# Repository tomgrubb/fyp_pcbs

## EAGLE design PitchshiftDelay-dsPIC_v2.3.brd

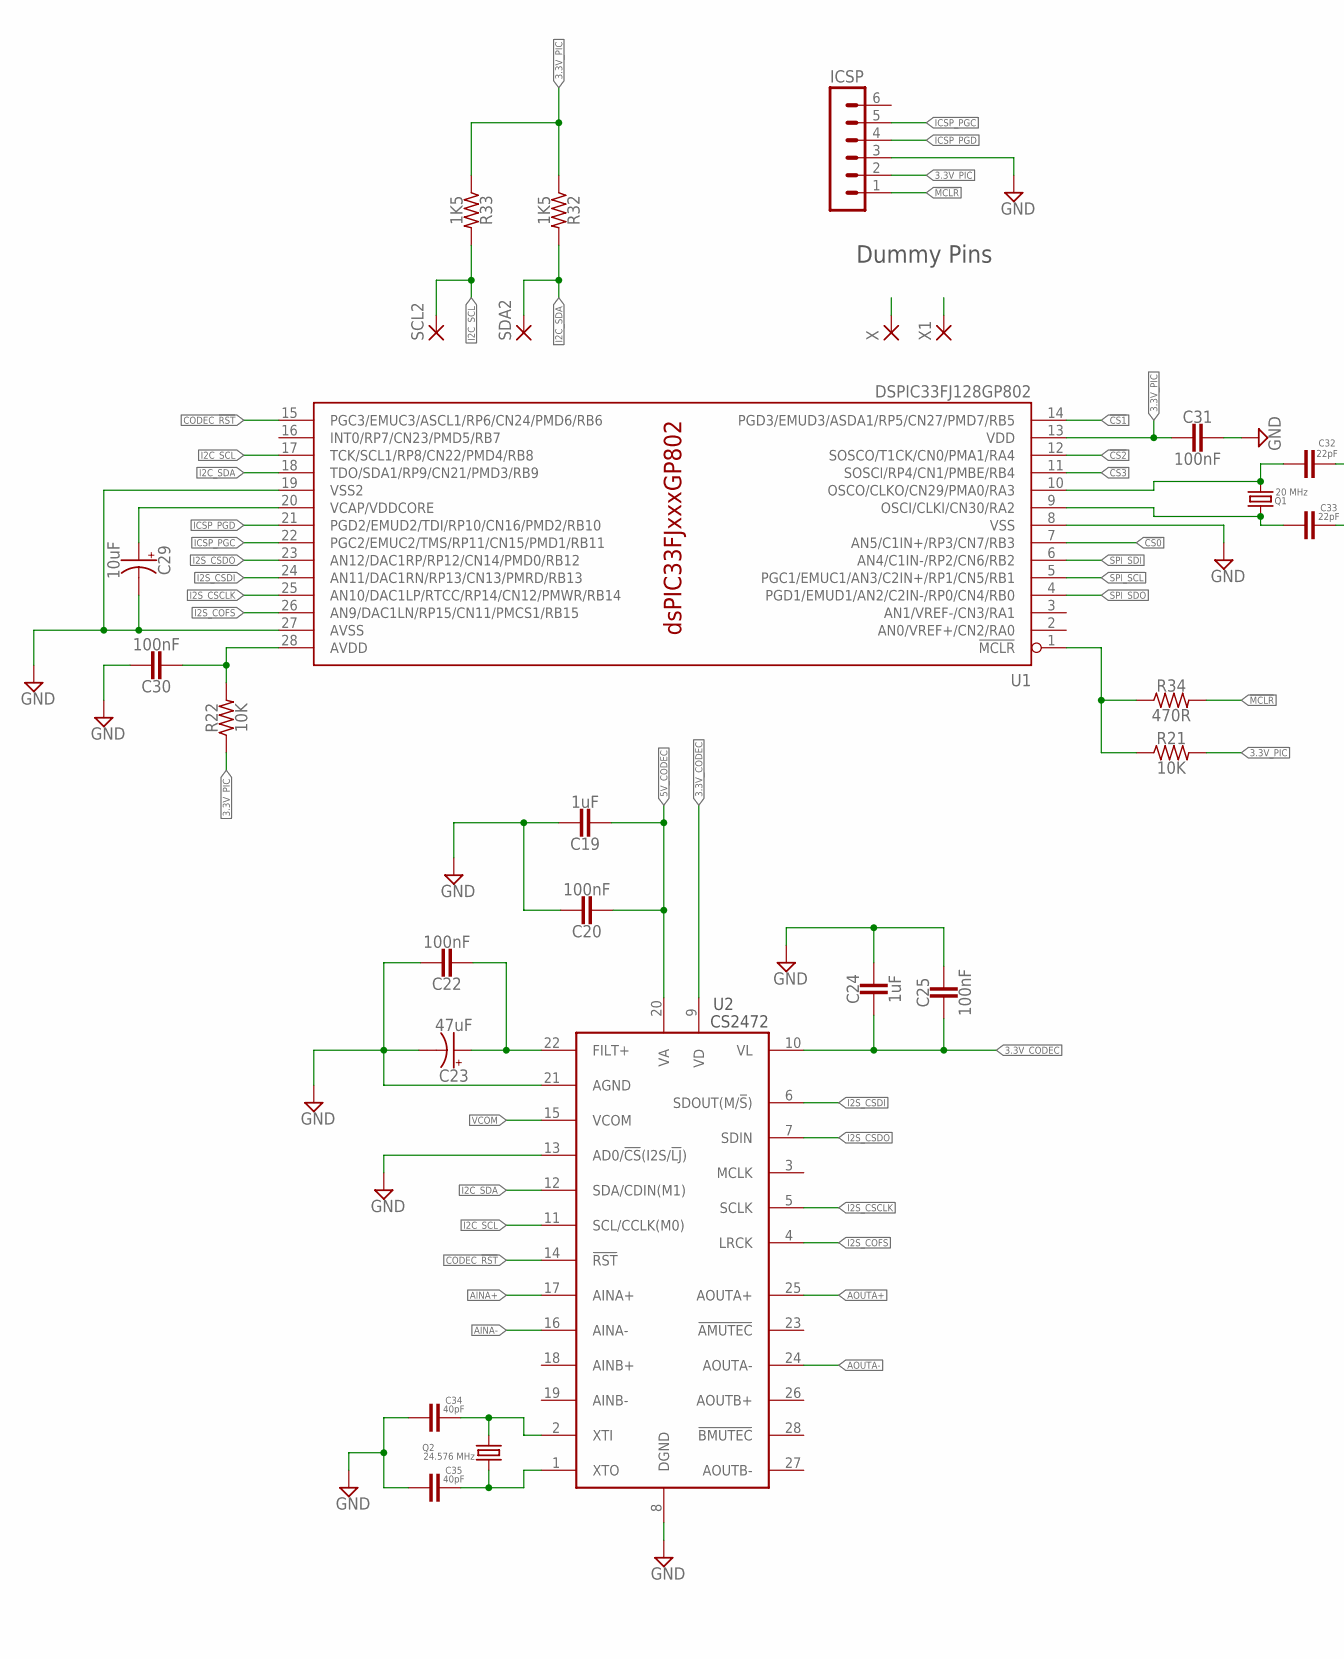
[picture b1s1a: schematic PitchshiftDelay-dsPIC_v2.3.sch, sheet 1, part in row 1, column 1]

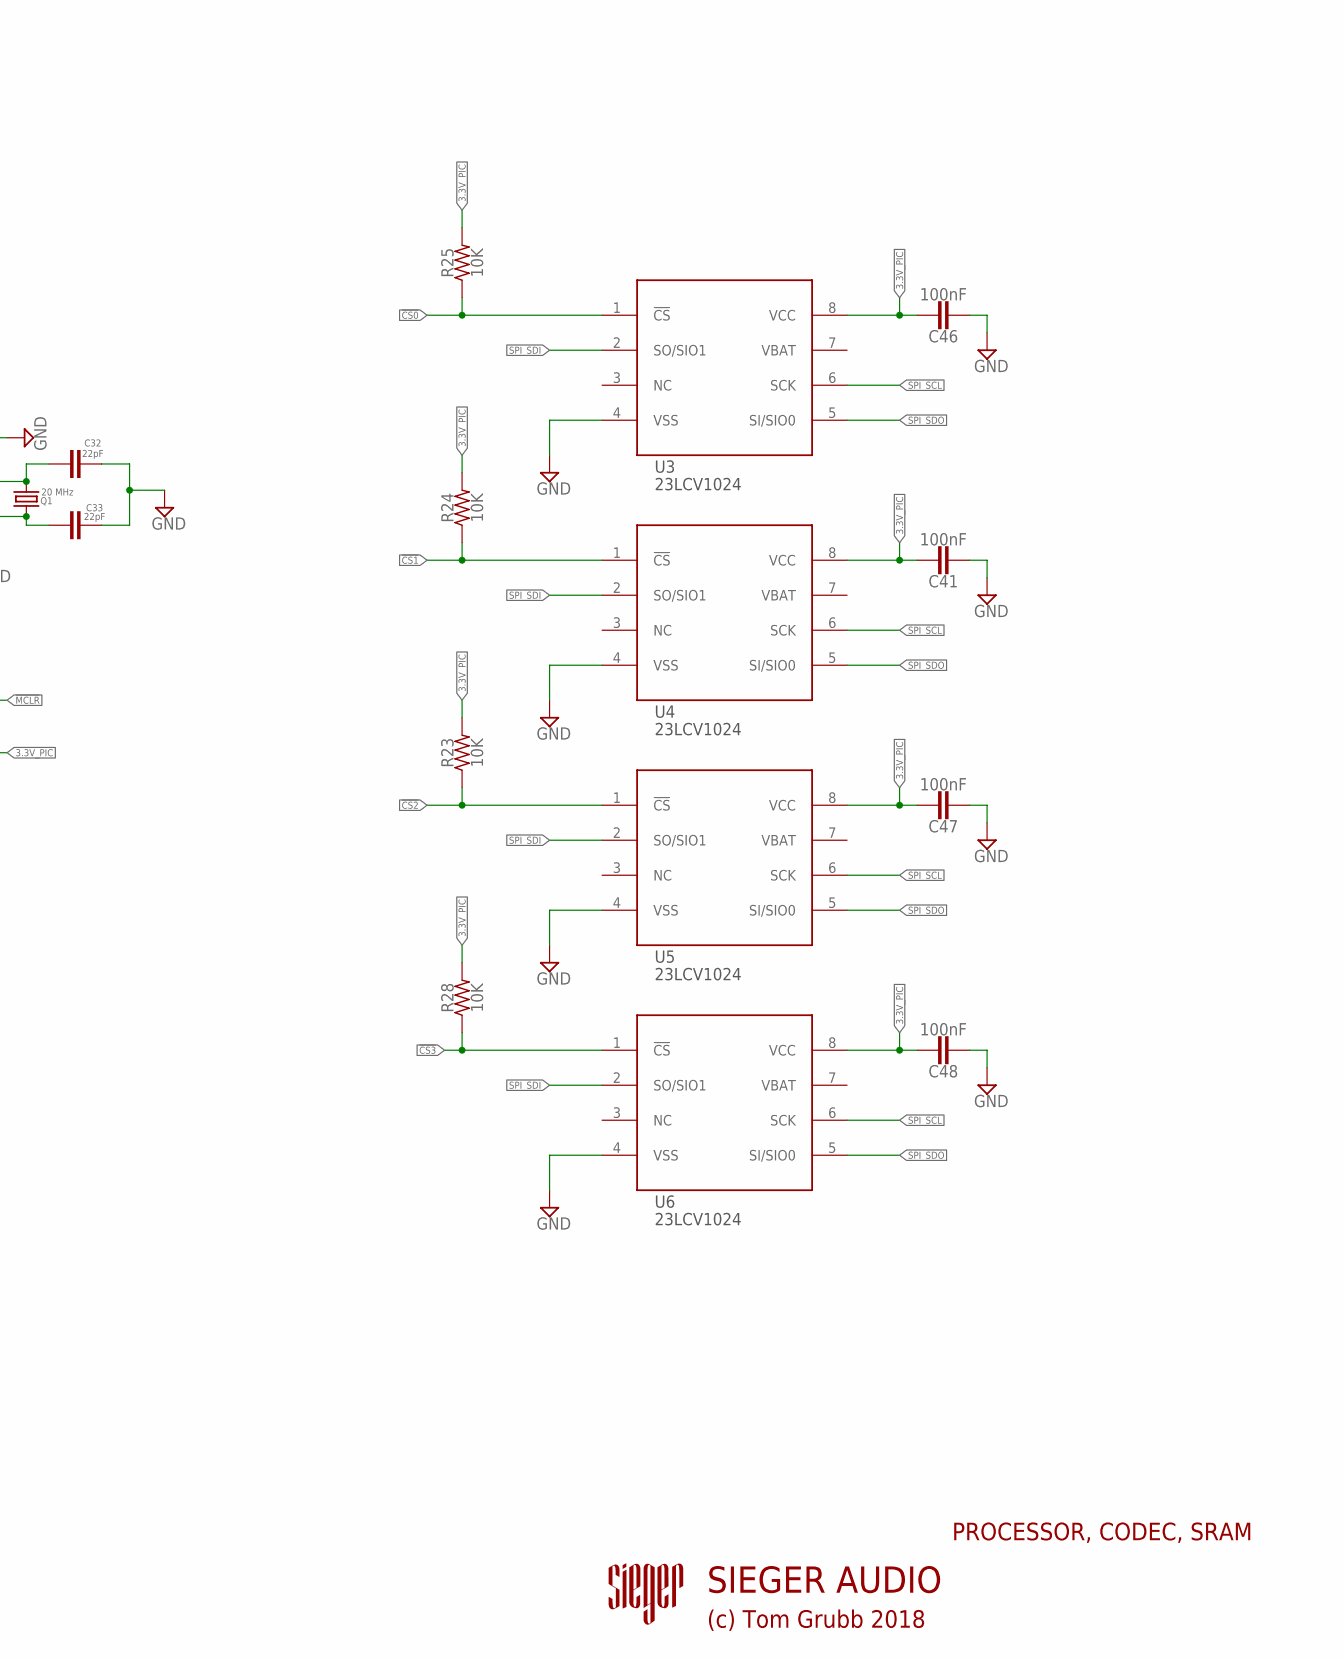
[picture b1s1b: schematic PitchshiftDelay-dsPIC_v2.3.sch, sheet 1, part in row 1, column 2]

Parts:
C19, C24: 1uF; 050X030_025
C20, C22, C25, C30, C31, C41, C46, C47, C48: 100nF; 050X030_025
C23: 47uF; 050_020_1
C29: 10uF; 050_020_1B
C32, C33: 22pF; 0805
C34, C35: 40pF; 0805
ICSP: MA06-1
Q1: 20 MHz; HC49U-V
Q2: 24.576 MHz; HC49U-V
R21, R22, R23, R24, R25, R28: 10K; RESISTOR_C0805
R32, R33: 1K5; RESISTOR_C0805
R34: 470R; RESISTOR_C0805
SCL2: 2,15/1,0
SDA2: 2,15/1,0
U1: DSPIC33FJ128GP802; SO28W
U2: CS2472; TSSOP28L
U3, U4, U5, U6: 23LCV1024; SOIC8
X, X1: 2,15/1,0

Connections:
3.3V_CODEC: C24.2, C25.2, U2.9 (VD), U2.10 (VL); also elsewhere on the board
3.3V_PIC: C31.2, C41.1, C46.1, C47.1, C48.1, ICSP.2, R21.2, R22.1, R23.2, R24.2, R25.2, R28.2, R32.1, R33.1, U1.13 (VDD), U3.8 (VCC), U4.8 (VCC), U5.8 (VCC), U6.8 (VCC); also elsewhere on the board
5V_CODEC: C19.2, C20.2, U2.20 (VA); also elsewhere on the board
!CS0: R25.1, U1.7 (AN5/C1IN+/RP3/CN7/RB3), U3.1 (!CS)
!CS1: R24.1, U1.14 (PGD3/EMUD3/ASDA1/RP5/CN27/PMD7/RB5), U4.1 (!CS)
!CS2: R23.1, U1.12 (SOSCO/T1CK/CN0/PMA1/RA4), U5.1 (!CS)
!CS3: R28.1, U1.11 (SOSCI/RP4/CN1/PMBE/RB4), U6.1 (!CS)
!MCLR: ICSP.1, R34.2
AINA+: U2.17 (AINA+); also elsewhere on the board
AINA-: U2.16 (AINA-); also elsewhere on the board
AOUTA+: U2.25 (AOUTA+); also elsewhere on the board
AOUTA-: U2.24 (AOUTA-); also elsewhere on the board
CODEC_!RST: U1.15 (PGC3/EMUC3/ASCL1/RP6/CN24/PMD6/RB6), U2.14 (!RST)
FILT+: C22.2, C23.+, U2.22 (FILT+)
GND: C19.1, C20.1, C22.1, C23.-, C24.1, C25.1, C29.-, C30.1, C31.1, C32.1, C33.1, C34.2, C35.2, C41.2, C46.2, C47.2, C48.2, ICSP.3, U1.8 (VSS), U1.19 (VSS2), U1.27 (AVSS), U2.8 (DGND), U2.13 (AD0/!CS!(I2S/!LJ!)), U2.21 (AGND), U3.4 (VSS), U4.4 (VSS), U5.4 (VSS), U6.4 (VSS); also elsewhere on the board
I2C_SCL: R33.2, SCL2.1, U1.17 (TCK/SCL1/RP8/CN22/PMD4/RB8), U2.11 (SCL/CCLK(M0)), X.1
I2C_SDA: R32.2, SDA2.1, U1.18 (TDO/SDA1/RP9/CN21/PMD3/RB9), U2.12 (SDA/CDIN(M1))
I2S_COFS: U1.26 (AN9/DAC1LN/RP15/CN11/PMCS1/RB15), U2.4 (LRCK)
I2S_CSCLK: U1.25 (AN10/DAC1LP/RTCC/RP14/CN12/PMWR/RB14), U2.5 (SCLK)
I2S_CSDI: U1.24 (AN11/DAC1RN/RP13/CN13/PMRD/RB13), U2.6 (SDOUT(M/!S!))
I2S_CSDO: U1.23 (AN12/DAC1RP/RP12/CN14/PMD0/RB12), U2.7 (SDIN)
ICSP_PGC: ICSP.5, U1.22 (PGC2/EMUC2/TMS/RP11/CN15/PMD1/RB11)
ICSP_PGD: ICSP.4, U1.21 (PGD2/EMUD2/TDI/RP10/CN16/PMD2/RB10)
unnamed: C30.2, R22.2, U1.28 (AVDD)
unnamed: C29.+, U1.20 (VCAP/VDDCORE)
unnamed: C33.2, Q1.1, U1.9 (OSCI/CLKI/CN30/RA2)
unnamed: C32.2, Q1.2, U1.10 (OSCO/CLKO/CN29/PMA0/RA3)
unnamed: R21.1, R34.1, U1.1 (!MCLR)
unnamed: C34.1, Q2.2, U2.2 (XTI)
unnamed: C35.1, Q2.1, U2.1 (XTO)
SPI_SCL: U1.5 (PGC1/EMUC1/AN3/C2IN+/RP1/CN5/RB1), U3.6 (SCK), U4.6 (SCK), U5.6 (SCK), U6.6 (SCK)
SPI_SDI: U1.6 (AN4/C1IN-/RP2/CN6/RB2), U3.2 (SO/SIO1), U4.2 (SO/SIO1), U5.2 (SO/SIO1), U6.2 (SO/SIO1)
SPI_SDO: U1.4 (PGD1/EMUD1/AN2/C2IN-/RP0/CN4/RB0), U3.5 (SI/SIO0), U4.5 (SI/SIO0), U5.5 (SI/SIO0), U6.5 (SI/SIO0)
VCOM: U2.15 (VCOM); also elsewhere on the board

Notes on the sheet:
PROCESSOR, CODEC, SRAM
Dummy Pins
(c) Tom Grubb 2018
SIEGER AUDIO

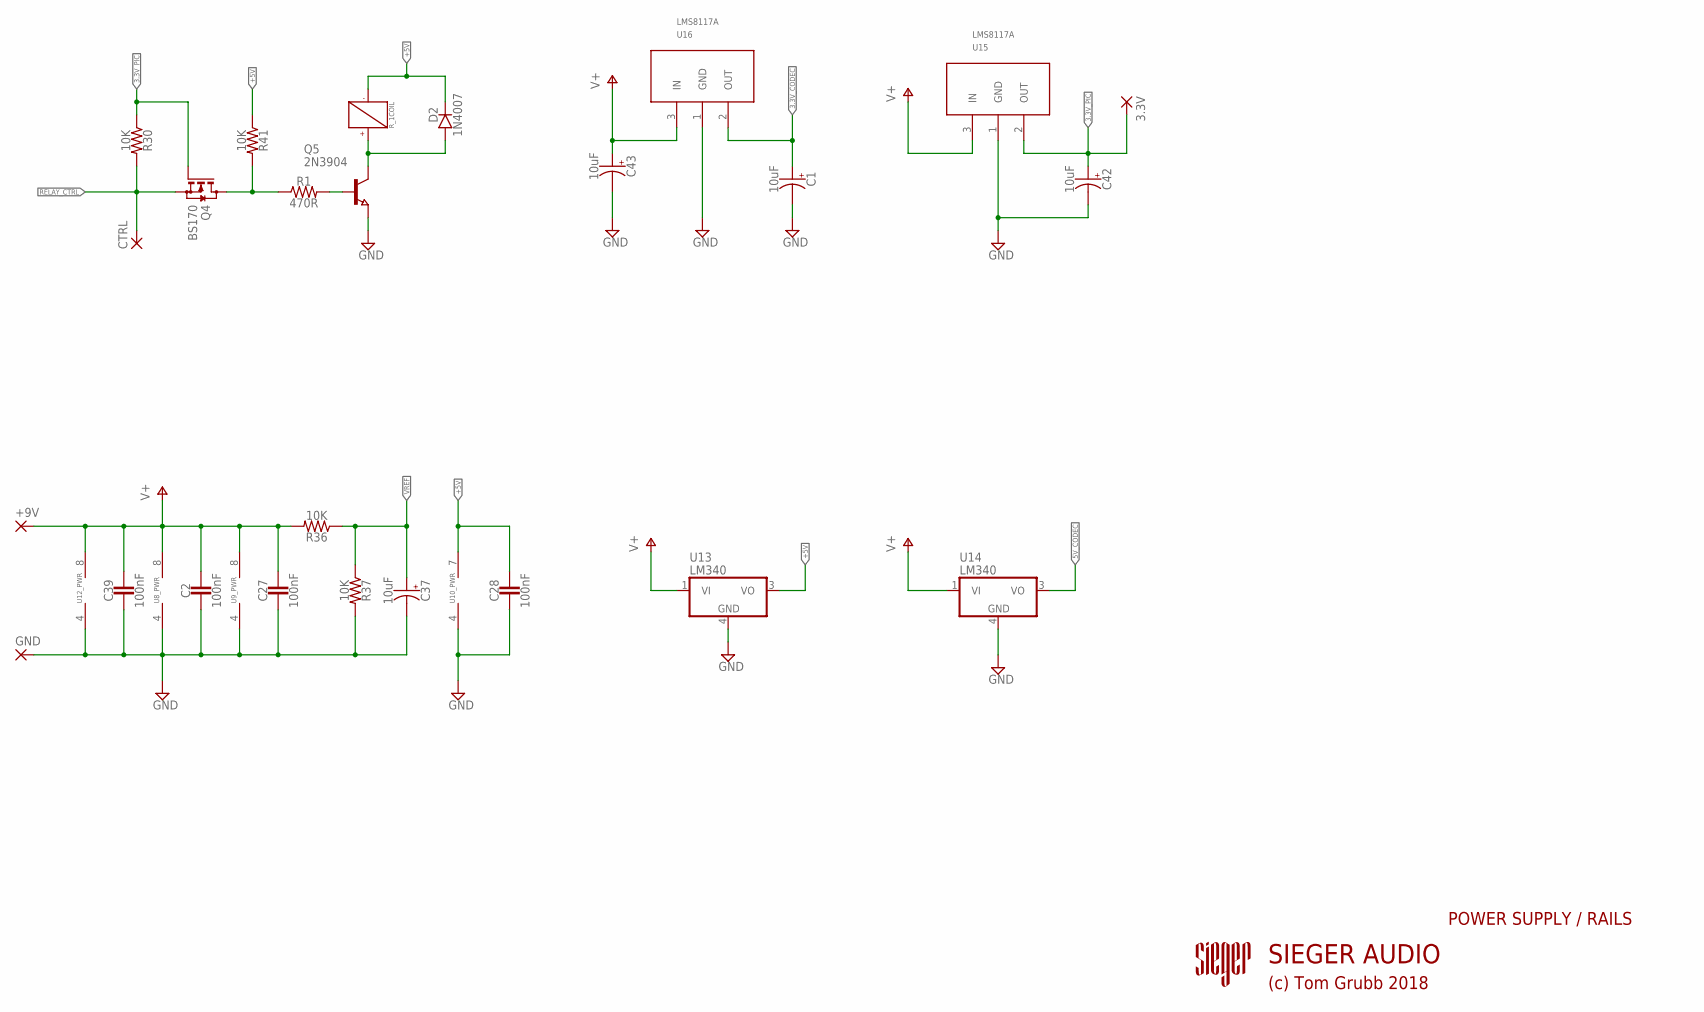
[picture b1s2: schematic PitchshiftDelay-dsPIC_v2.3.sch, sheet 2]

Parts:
3.3V: 2,15/1,0
+9V: 2,15/1,0
C1, C37, C42, C43: 10uF; 050_020_1
C2, C27, C28, C39: 100nF; 050X030_025
CTRL: 2,15/1,0
D2: 1N4007; DO35-3
GND: 2,15/1,0
Q4: BS170; SOT23
Q5: 2N3904; SOT23
R1: 470R; RESISTOR_C0805
R30, R36, R37, R41: 10K; RESISTOR_C0805
R_1: AL5WNK_2; 10PIN
U8, U9, U12: LF353; SO08
U10: OP1177; MSOP8
U13, U14: LM340; SOT223
U15, U16: LMS8117A; SOT223

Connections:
3.3V_CODEC: C1.+, U16.2 (OUT); also elsewhere on the board
3.3V_PIC: 3.3V.1, C42.+, Q4.1 (G), R30.1, U15.2 (OUT); also elsewhere on the board
5V_CODEC: U14.3 (VO); also elsewhere on the board
+5V: C28.1, D2.C, R41.1, R_1.P$10 (-), U10.7 (V+), U13.3 (VO); also elsewhere on the board
GND: C1.-, C2.2, C27.2, C28.2, C37.-, C39.2, C42.-, C43.-, GND.1, Q5.2 (E), R37.2, U8.4 (V-), U9.4 (V-), U10.4 (V-), U12.4 (V-), U13.4 (GND), U14.4 (GND), U15.1 (GND), U16.1 (GND); also elsewhere on the board
unnamed: Q5.1 (B), R1.2
unnamed: D2.A, Q5.3 (C), R_1.P$1 (+)
unnamed: Q4.3 (D), R1.1, R41.2
RELAY_CTRL: CTRL.1, Q4.2 (S), R30.2
V+: +9V.1, C2.1, C27.1, C39.1, C43.+, R36.2, U8.8 (V+), U9.8 (V+), U12.8 (V+), U13.1 (VI), U14.1 (VI), U15.3 (IN), U16.3 (IN)
VREF: C37.+, R36.1, R37.1; also elsewhere on the board

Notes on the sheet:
POWER SUPPLY / RAILS
(c) Tom Grubb 2018
SIEGER AUDIO

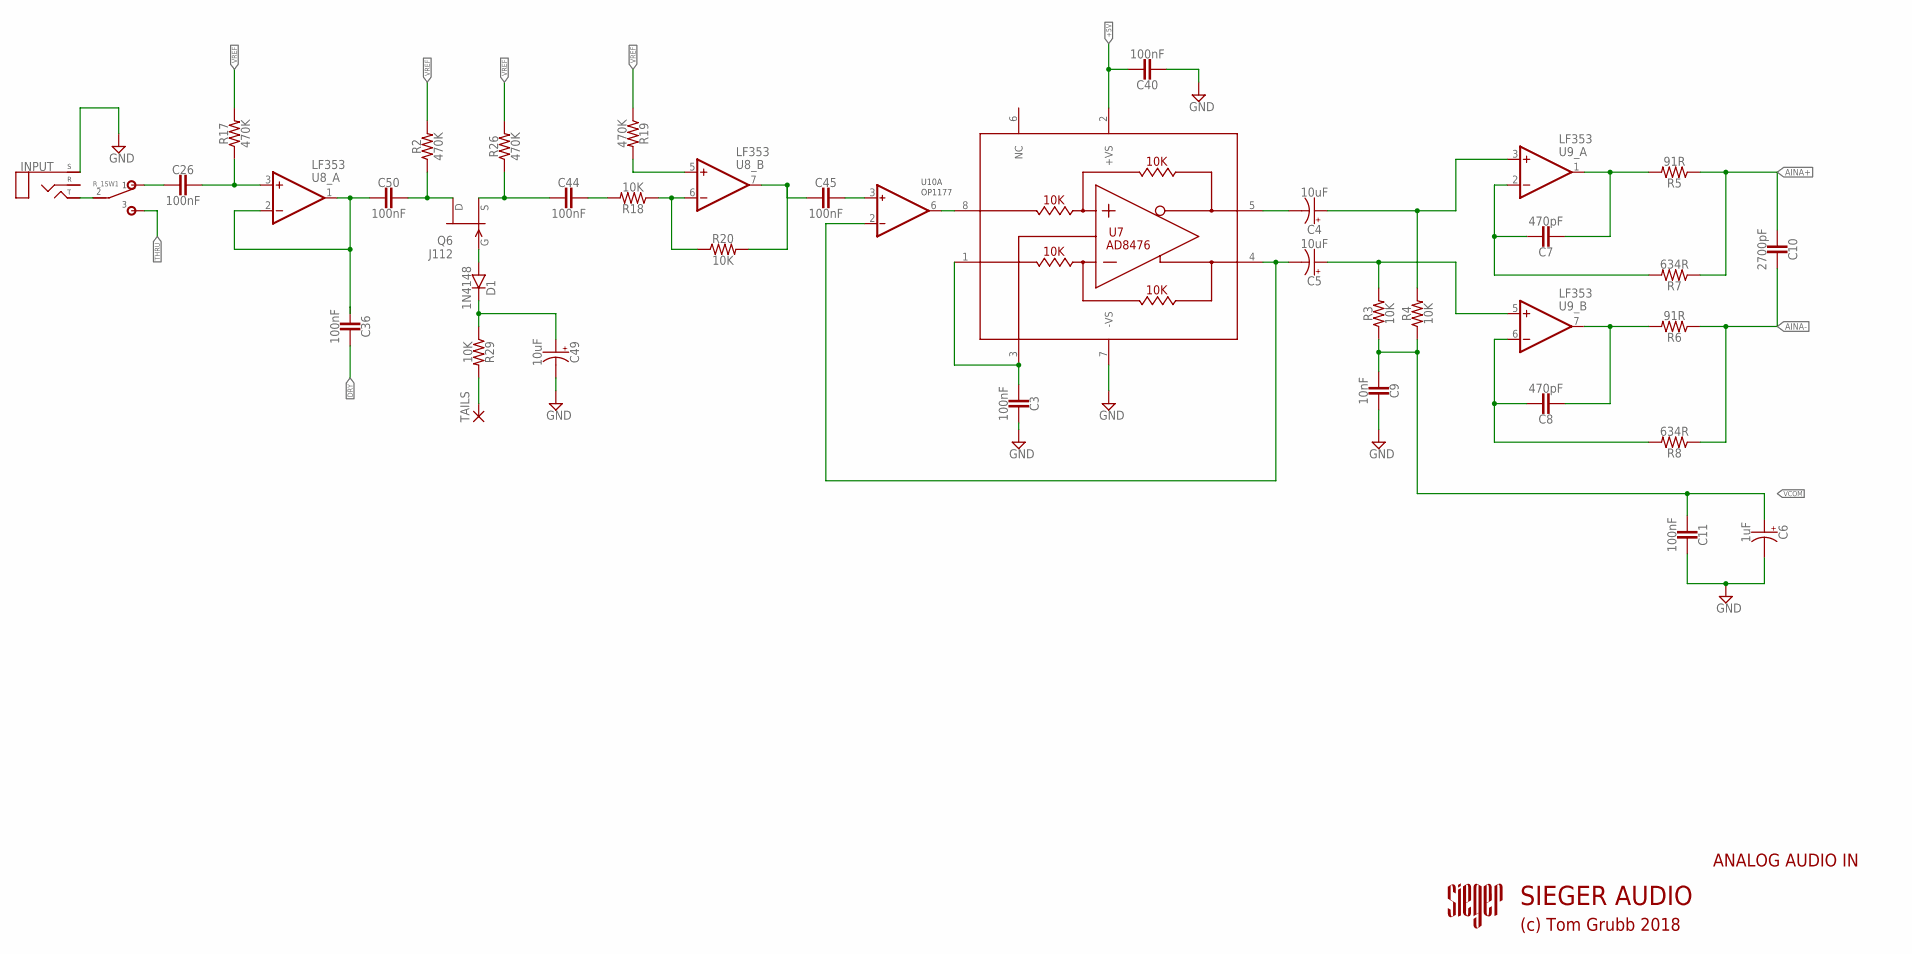
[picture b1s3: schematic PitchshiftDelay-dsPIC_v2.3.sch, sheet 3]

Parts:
C3, C11, C40: 100nF; 050X030_025
C4, C5, C49: 10uF; 050_020_1
C6: 1uF; 050_020_1
C7, C8: 470pF; BOX_SMALL
C9: 10nF; 050X030_025
C10: 2700pF; BOX_SMALL
C26, C36, C44, C45, C50: 100nF; BOX_SMALL
D1: 1N4148; DO35-3
INPUT: STEREO; STEREO_PCB
Q6: J112; SOT23
R2, R17, R19, R26: 470K; RESISTOR_C0805
R3, R4, R18, R20, R29: 10K; RESISTOR_C0805
R5, R6: 91R; RESISTOR_C0805
R7, R8: 634R; RESISTOR_C0805
R_1: AL5WNK_2; 10PIN
TAILS: 2,15/1,0
U7: AD8476; MSOP8
U8, U9: LF353; SO08
U10: OP1177; MSOP8

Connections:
+5V: C40.1, U7.2 (+VS); also elsewhere on the board
AINA+: C10.2, R5.1, R7.1; also elsewhere on the board
AINA-: C10.1, R6.1, R8.1; also elsewhere on the board
DRY: C36.1; also elsewhere on the board
GND: C3.1, C6.-, C9.1, C11.1, C40.2, C49.-, INPUT.P$1 (S), U7.7 (-VS); also elsewhere on the board
unnamed: C45.1, U10.3 (+IN)
unnamed: C3.2, U7.1 (IN-), U7.3 (VCOM)
unnamed: U7.8 (IN+), U10.6 (OUT)
unnamed: C5.-, U7.4 (+OUT), U10.2 (-IN)
unnamed: C36.2, C50.2, U8.1 (OUT), U8.2 (-IN)
unnamed: C26.1, R17.1, U8.3 (+IN)
unnamed: C4.-, U7.5 (-OUT)
unnamed: C5.+, R3.2, U9.5 (+IN)
unnamed: C4.+, R4.2, U9.3 (+IN)
unnamed: C8.1, R8.2, U9.6 (-IN)
unnamed: C8.2, R6.2, U9.7 (OUT)
unnamed: C7.1, R7.2, U9.2 (-IN)
unnamed: C7.2, R5.2, U9.1 (OUT)
unnamed: C26.2, R_1.P$2 (1)
unnamed: R18.1, R20.1, U8.6 (-IN)
unnamed: R19.2, U8.5 (+IN)
unnamed: C50.1, Q6.1 (D), R2.1
unnamed: C45.2, R20.2, U8.7 (OUT)
unnamed: C44.1, R18.2
unnamed: INPUT.P$3 (T), R_1.P$3 (2)
unnamed: C44.2, Q6.2 (S), R26.1
unnamed: C49.+, D1.C, R29.1
unnamed: D1.A, Q6.3 (G)
unnamed: R29.2, TAILS.1
THRU: R_1.P$4 (3); also elsewhere on the board
VCOM: C6.+, C9.2, C11.2, R3.1, R4.1; also elsewhere on the board
VREF: R2.2, R17.2, R19.1, R26.2; also elsewhere on the board

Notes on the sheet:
ANALOG AUDIO IN
(c) Tom Grubb 2018
SIEGER AUDIO

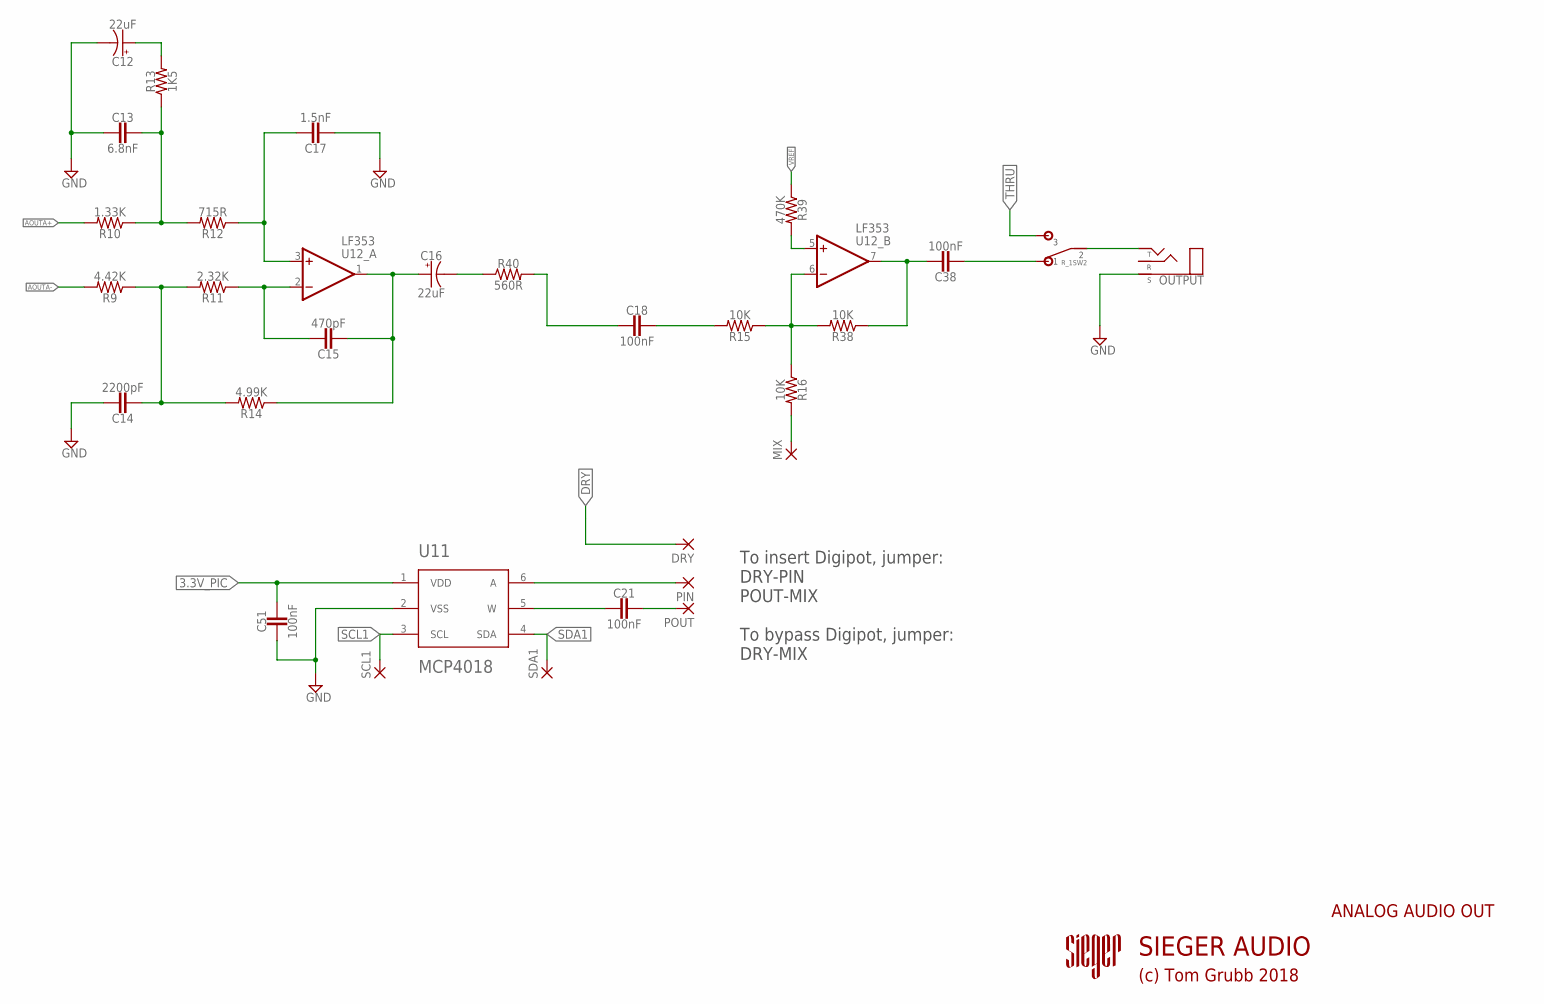
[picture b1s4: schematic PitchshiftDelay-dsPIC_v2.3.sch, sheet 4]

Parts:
C12, C16: 22uF; 050_020_1
C13: 6.8nF; BOX_SMALL
C14: 2200pF; BOX_SMALL
C15: 470pF; BOX_SMALL
C17: 1.5nF; BOX_SMALL
C18, C21, C38: 100nF; BOX_SMALL
C51: 100nF; 050X030_025
DRY: 2,15/1,0
MIX: 2,15/1,0
OUTPUT: STEREO; STEREO_PCB
PIN: 2,15/1,0
POUT: 2,15/1,0
R9: 4.42K; RESISTOR_C0805
R10: 1.33K; RESISTOR_C0805
R11: 2.32K; RESISTOR_C0805
R12: 715R; RESISTOR_C0805
R13: 1K5; RESISTOR_C0805
R14: 4.99K; RESISTOR_C0805
R15, R16, R38: 10K; RESISTOR_C0805
R39: 470K; RESISTOR_C0805
R40: 560R; RESISTOR_C0805
R_1: AL5WNK_2; 10PIN
SCL1: 2,15/1,0
SDA1: 2,15/1,0
U11: MCP4018; SC70-6
U12: LF353; SO08

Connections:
3.3V_PIC: C51.1, U11.1 (VDD); also elsewhere on the board
AMUTE: C18.2, R40.2
AOUTA+: R10.2; also elsewhere on the board
AOUTA-: R9.2; also elsewhere on the board
DRY: DRY.1; also elsewhere on the board
GND: C12.-, C13.2, C14.1, C17.2, C51.2, OUTPUT.P$1 (S), U11.2 (VSS); also elsewhere on the board
unnamed: C21.2, U11.5 (W)
unnamed: C16.-, R40.1
unnamed: C13.1, R10.1, R12.2, R13.1
unnamed: C14.2, R9.1, R11.2, R14.2
unnamed: C15.1, R11.1, U12.2 (-IN)
unnamed: C17.1, R12.1, U12.3 (+IN)
unnamed: C15.2, C16.+, R14.1, U12.1 (OUT)
unnamed: MIX.1, R16.2
unnamed: C18.1, R15.2
unnamed: C12.+, R13.2
unnamed: OUTPUT.P$3 (T), R_1.P$8 (2)
unnamed: C38.2, R_1.P$9 (1)
unnamed: PIN.1, U11.6 (A)
unnamed: R15.1, R16.1, R38.2, U12.6 (-IN)
unnamed: C38.1, R38.1, U12.7 (OUT)
unnamed: R39.2, U12.5 (+IN)
unnamed: C21.1, POUT.1
SCL1: SCL1.1, U11.3 (SCL)
SDA1: SDA1.1, U11.4 (SDA)
THRU: R_1.P$7 (3); also elsewhere on the board
VREF: R39.1; also elsewhere on the board

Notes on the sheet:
To insert Digipot, jumper: DRY-PIN POUT-MIX To bypass Digipot, jumper: DRY-MIX
ANALOG AUDIO OUT
(c) Tom Grubb 2018
SIEGER AUDIO

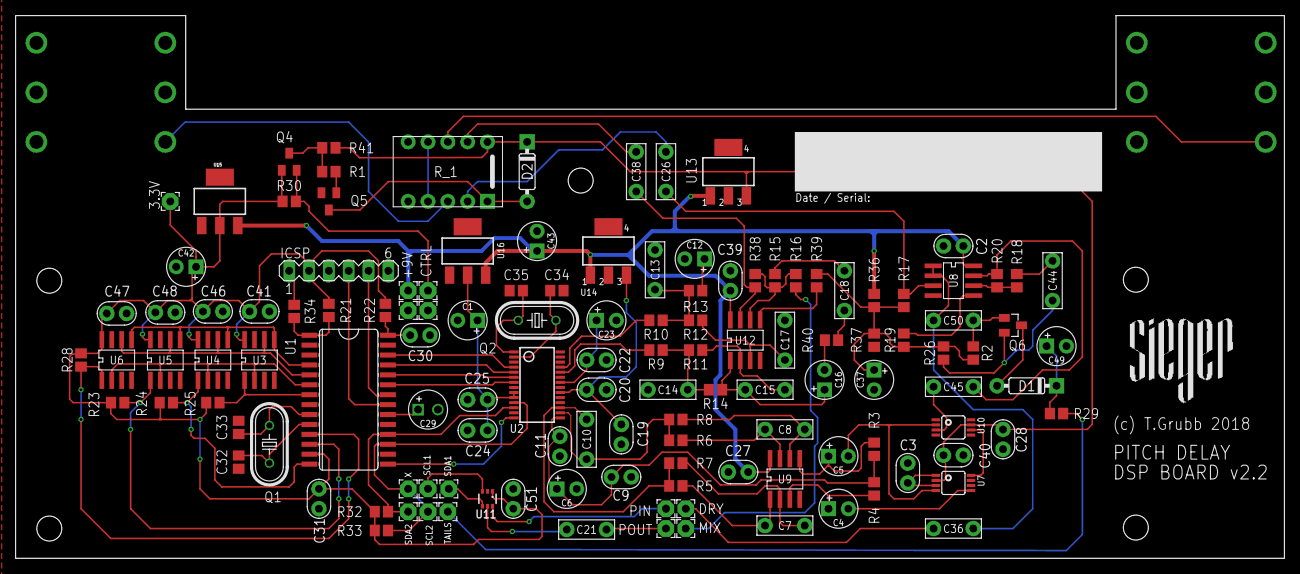
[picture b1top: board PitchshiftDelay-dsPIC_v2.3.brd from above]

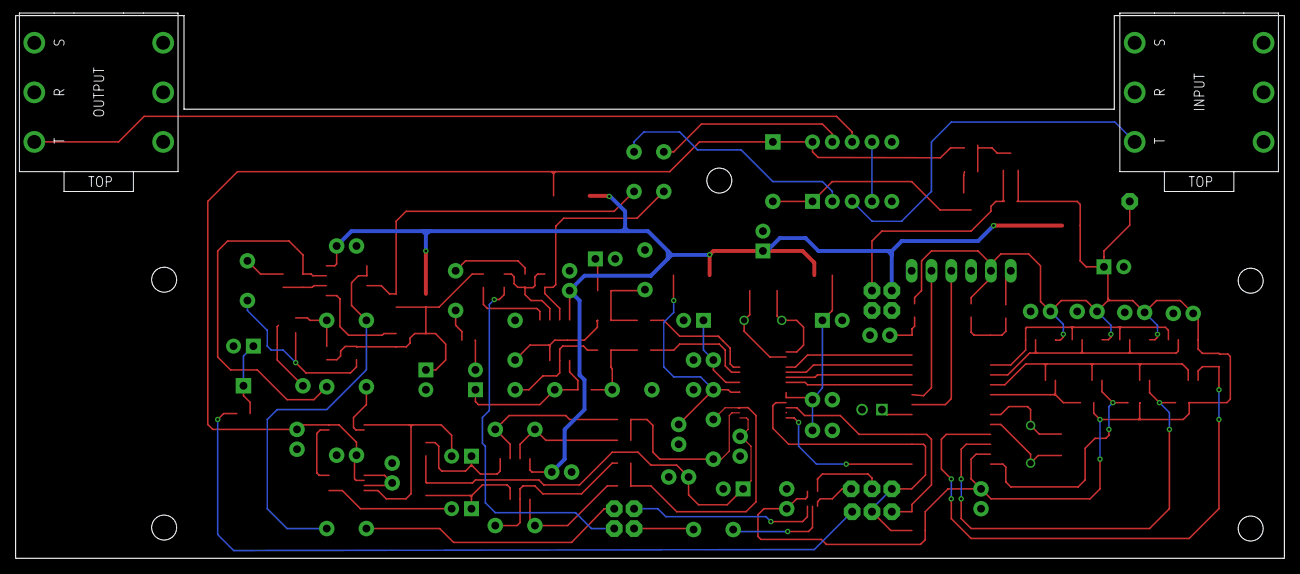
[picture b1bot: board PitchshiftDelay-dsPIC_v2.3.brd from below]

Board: 2 copper layers, 162.5 x 69.5 mm, 132 parts (2 on the bottom side), 87 nets.

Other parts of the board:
U$1: LARGE

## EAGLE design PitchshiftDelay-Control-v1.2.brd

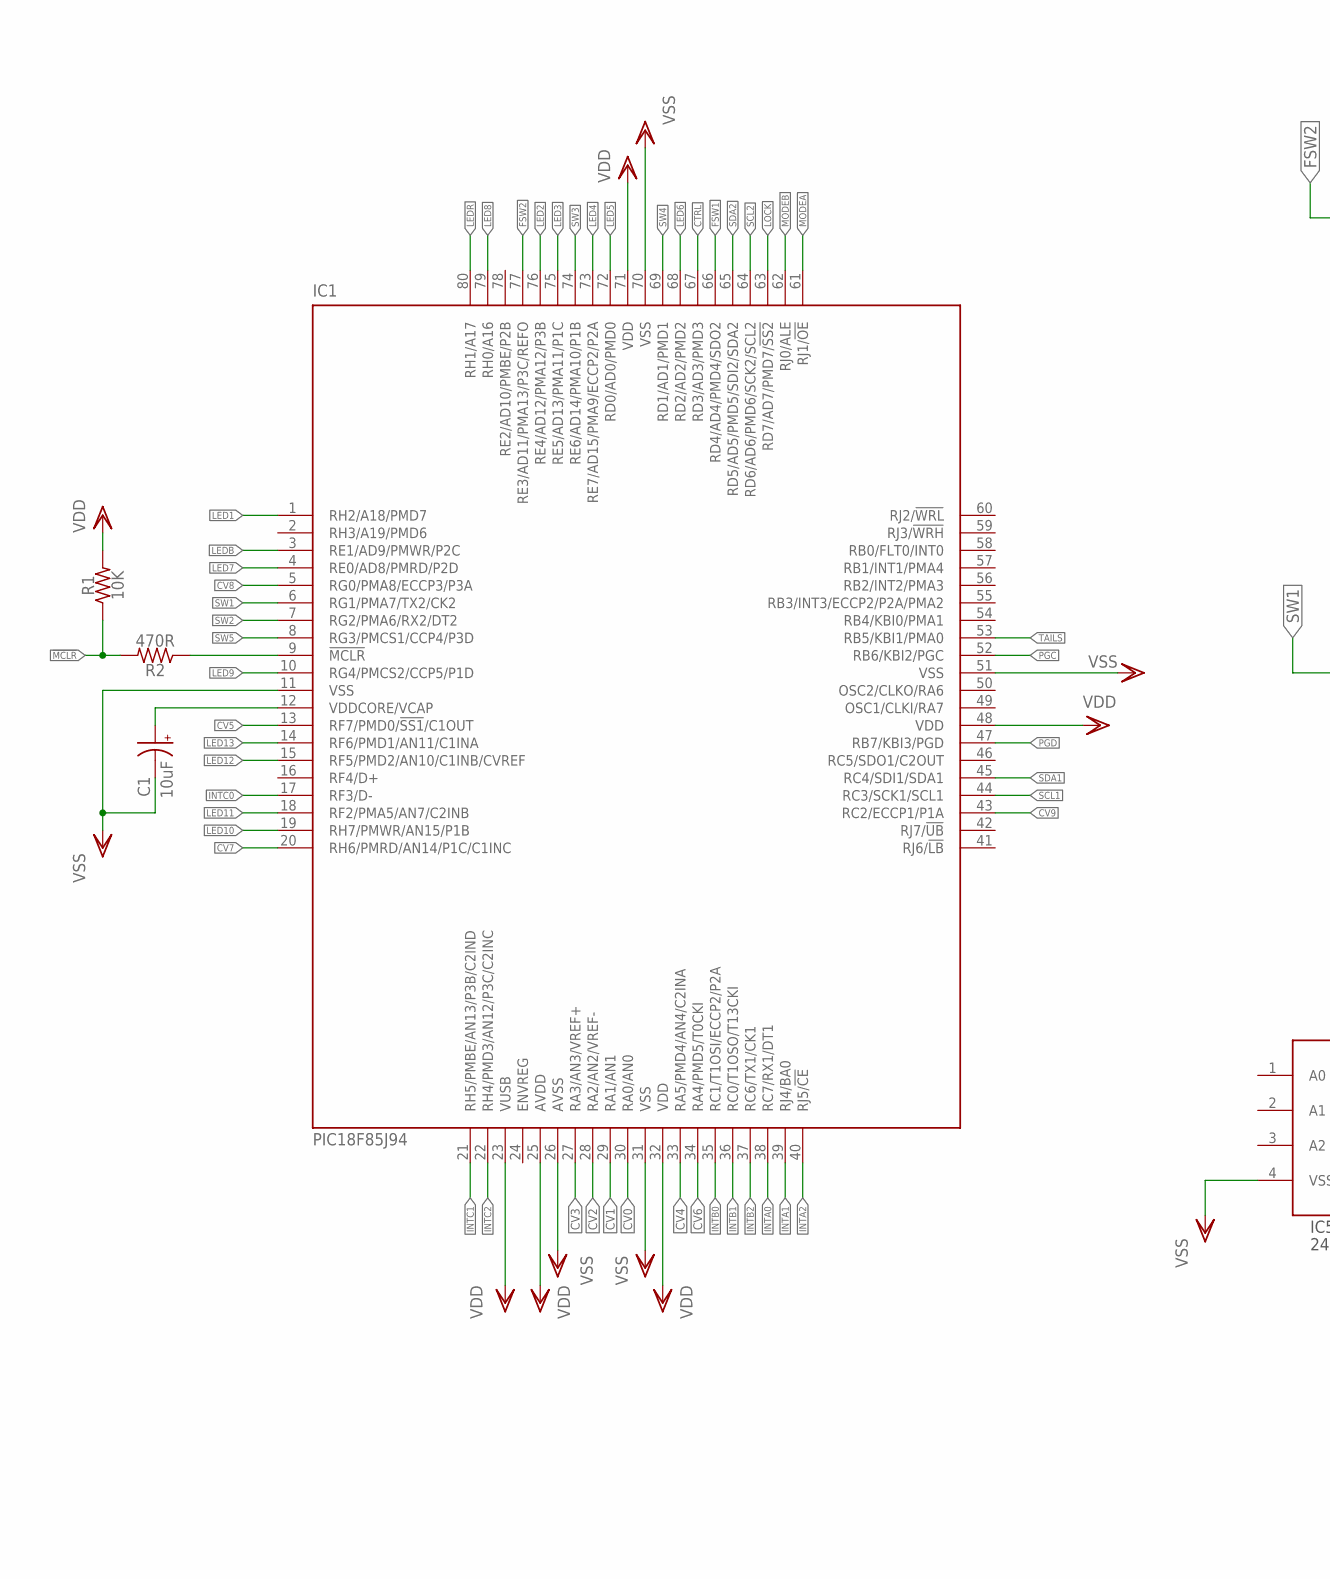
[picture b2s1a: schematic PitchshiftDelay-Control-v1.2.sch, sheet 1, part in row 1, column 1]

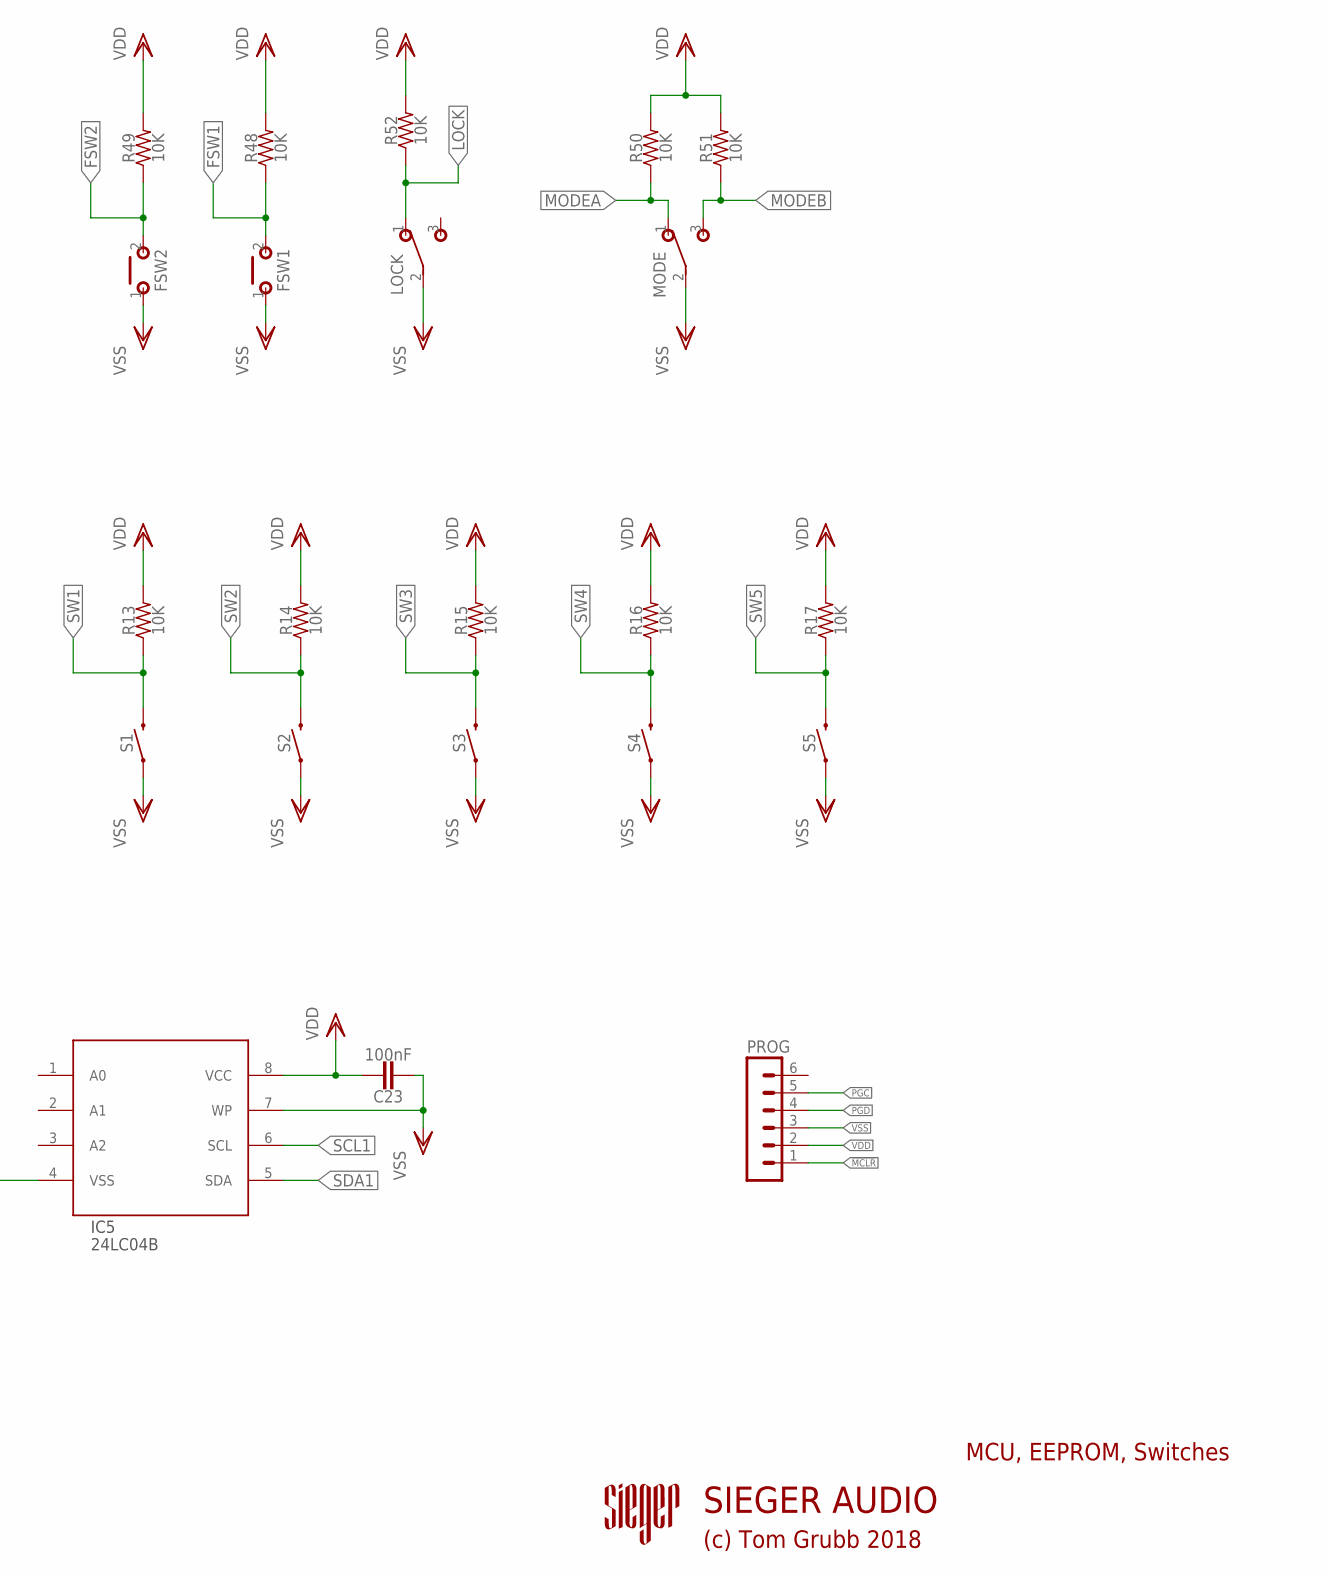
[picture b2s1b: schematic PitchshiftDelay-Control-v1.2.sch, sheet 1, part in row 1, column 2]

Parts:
C1: 10uF; 050_020_1
C23: 100nF; 050X030_025
FSW1, FSW2: MOMENTARY; SPST
IC1: PIC18F85J94; TQFP80-12X12
IC5: 24LC04B; SOIC8
LOCK: SPDTPIN_MOUNT; 1MS1T1B1C0M2QE
MODE: SPDTPIN_MOUNT; 1MS1T1B1C0M2QE
PROG: MA06-1
R1, R13, R14, R15, R16, R17, R48, R49, R50, R51, R52: 10K; RESISTOR_C0805
R2: 470R; RESISTOR_C0805
S1, S2, S3, S4, S5: MOMENTARY-SWITCH-SPST-PTH-6.0MM; TACTILE_SWITCH_PTH_6.0MM

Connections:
!MCLR: PROG.1, R1.1, R2.2
CTRL: IC1.67 (RD3/AD3/PMD3); also elsewhere on the board
CV0: IC1.30 (RA0/AN0); also elsewhere on the board
CV1: IC1.29 (RA1/AN1); also elsewhere on the board
CV2: IC1.28 (RA2/AN2/VREF-); also elsewhere on the board
CV3: IC1.27 (RA3/AN3/VREF+); also elsewhere on the board
CV4: IC1.33 (RA5/PMD4/AN4/C2INA); also elsewhere on the board
CV5: IC1.13 (RF7/PMD0/!SS1!/C1OUT); also elsewhere on the board
CV6: IC1.34 (RA4/PMD5/T0CKI); also elsewhere on the board
CV7: IC1.20 (RH6/PMRD/AN14/P1C/C1INC); also elsewhere on the board
CV8: IC1.5 (RG0/PMA8/ECCP3/P3A); also elsewhere on the board
CV9: IC1.43 (RC2/ECCP1/P1A); also elsewhere on the board
FSW1: FSW1.2 (S), IC1.66 (RD4/AD4/PMD4/SDO2), R48.1
FSW2: FSW2.2 (S), IC1.77 (RE3/AD11/PMA13/P3C/REFO), R49.1
INTA0: IC1.38 (RC7/RX1/DT1); also elsewhere on the board
INTA1: IC1.39 (RJ4/BA0); also elsewhere on the board
INTA2: IC1.40 (RJ5/!CE); also elsewhere on the board
INTB0: IC1.35 (RC1/T1OSI/ECCP2/P2A); also elsewhere on the board
INTB1: IC1.36 (RC0/T1OSO/T13CKI); also elsewhere on the board
INTB2: IC1.37 (RC6/TX1/CK1); also elsewhere on the board
INTC0: IC1.17 (RF3/D-); also elsewhere on the board
INTC1: IC1.21 (RH5/PMBE/AN13/P3B/C2IND); also elsewhere on the board
INTC2: IC1.22 (RH4/PMD3/AN12/P3C/C2INC); also elsewhere on the board
LED1: IC1.1 (RH2/A18/PMD7); also elsewhere on the board
LED2: IC1.76 (RE4/AD12/PMA12/P3B); also elsewhere on the board
LED3: IC1.75 (RE5/AD13/PMA11/P1C); also elsewhere on the board
LED4: IC1.73 (RE7/AD15/PMA9/ECCP2/P2A); also elsewhere on the board
LED5: IC1.72 (RD0/AD0/PMD0); also elsewhere on the board
LED6: IC1.68 (RD2/AD2/PMD2); also elsewhere on the board
LED7: IC1.4 (RE0/AD8/PMRD/P2D); also elsewhere on the board
LED8: IC1.79 (RH0/A16); also elsewhere on the board
LED9: IC1.10 (RG4/PMCS2/CCP5/P1D); also elsewhere on the board
LED10: IC1.19 (RH7/PMWR/AN15/P1B); also elsewhere on the board
LED11: IC1.18 (RF2/PMA5/AN7/C2INB); also elsewhere on the board
LED12: IC1.15 (RF5/PMD2/AN10/C1INB/CVREF); also elsewhere on the board
LED13: IC1.14 (RF6/PMD1/AN11/C1INA); also elsewhere on the board
LEDB: IC1.3 (RE1/AD9/PMWR/P2C); also elsewhere on the board
LEDR: IC1.80 (RH1/A17); also elsewhere on the board
LOCK: IC1.63 (RD7/AD7/PMD7/!SS2), LOCK.1 (O), R52.1
MODEA: IC1.61 (RJ1/!OE), MODE.1 (O), R50.1
MODEB: IC1.62 (RJ0/ALE), MODE.3 (S), R51.1
unnamed: C1.+, IC1.12 (VDDCORE/VCAP)
unnamed: IC1.9 (!MCLR), R2.1
PGC: IC1.52 (RB6/KBI2/PGC), PROG.5
PGD: IC1.47 (RB7/KBI3/PGD), PROG.4
SCL1: IC1.44 (RC3/SCK1/SCL1), IC5.6 (SCL); also elsewhere on the board
SCL2: IC1.64 (RD6/AD6/PMD6/SCK2/SCL2); also elsewhere on the board
SDA1: IC1.45 (RC4/SDI1/SDA1), IC5.5 (SDA); also elsewhere on the board
SDA2: IC1.65 (RD5/AD5/PMD5/SDI2/SDA2); also elsewhere on the board
SW1: IC1.6 (RG1/PMA7/TX2/CK2), R13.1, S1.3 (2)
SW2: IC1.7 (RG2/PMA6/RX2/DT2), R14.1, S2.3 (2)
SW3: IC1.74 (RE6/AD14/PMA10/P1B), R15.1, S3.3 (2)
SW4: IC1.69 (RD1/AD1/PMD1), R16.1, S4.3 (2)
SW5: IC1.8 (RG3/PMCS1/CCP4/P3D), R17.1, S5.3 (2)
TAILS: IC1.53 (RB5/KBI1/PMA0); also elsewhere on the board
VDD: C23.1, IC1.23 (VUSB), IC1.25 (AVDD), IC1.32 (VDD), IC1.48 (VDD), IC1.71 (VDD), IC5.8 (VCC), PROG.2, R1.2, R13.2, R14.2, R15.2, R16.2, R17.2, R48.2, R49.2, R50.2, R51.2, R52.2; also elsewhere on the board
VSS: C1.-, C23.2, FSW1.1, FSW2.1, IC1.11 (VSS), IC1.26 (AVSS), IC1.31 (VSS), IC1.51 (VSS), IC1.70 (VSS), IC5.4 (VSS), IC5.7 (WP), LOCK.2, MODE.2, PROG.3, S1.1, S2.1, S3.1, S4.1, S5.1; also elsewhere on the board

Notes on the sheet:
MCU, EEPROM, Switches
(c) Tom Grubb 2018
SIEGER AUDIO

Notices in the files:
parts and their libraries:
SparkFun-LED: Licensing: Creative Commons ShareAlike 4.0 International - https://creativecommons.org/licenses/by-sa/4.0
